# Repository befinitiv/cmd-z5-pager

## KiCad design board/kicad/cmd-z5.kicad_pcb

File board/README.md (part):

This document describes a PCB that acts as a replacement PCB for a Sony CMD-Z5 mobile phone. It is supposed to use the original screen and keyboard and turn the phone into a meshtastic device.

# Requirements

* nrf52840 CPU
* WIO-SX1262 wireless module with PCB antenna
* TBS M10N GPS with switched power line for power saving
* Battery charging and monitoring
* USB-C connector for charging and data/programming
* Use all keys of the original phone
* Use vibration motor, earpiece speaker and loudspeaker of original phone
* Use LEDs of original phone
* Uses small components so that PCB fits inside of housing
* Use 0402 passive components whenever possible
* Acceleromenter for movement detection
* Optimize for quiescent current. The device is also supposed to run in a low power mode where the idle current is expected to be below 20uA. This might require power switches to certain components.

# Component selection

LCSC part numbers were checked on 2026-10-02. Check stock again before ordering.

| Function | Part | LCSC | Package | Notes |
|---|---|---|---|---|
| MCU | Nordic nRF52840-QIAA-R | C190794 | aQFN-73 7×7 | Needs machine assembly |
| 32 MHz crystal | Yangxing X1E0000210163 | C91742 | 3225 | 10 pF, ±10 ppm |
| 32.768 kHz crystal | Epson X1A0000610006 | C99009 | 2012 | 7 pF |
| BLE antenna | Johanson 2450AT18A100E | C89334 | 1206 | Chip antenna with pi matching network |
| LoRa | Seeed Wio-SX1262 | – | 11.6×11 mm, 12 pins | **Not available on LCSC**; buy from Seeed. The standard version uses its IPEX connector and leaves the ANT pad (pin 9) unconnected; a PCB antenna needs the RF SMT-pin version (ask Seeed sales) |
| PMIC (charger, 2 bucks, 2 load switches, ADC, USB-C detection) | Nordic nPM1300-QEAA-R7 | C7501206 | QFN-32 5×5 | 0.8 µA battery current with a buck enabled, 370 nA in ship mode |
| GPS supply | TI TPS610997YFFR | C2072359 | DSBGA-6 | Fixed 5 V boost; EN fully disconnects the GPS (TBS M10N needs 3.6–5.5 V) |
| Accelerometer | ST LIS2DH12TR | C110926 | LGA-12 2×2 | About 2 µA in low-power motion detection; same WHO_AM_I as the LIS3DH. Alternative: LIS2DW12TR (C189624), lower current but needs its own driver |
| Earpiece amplifier | Diodes PAM8302AASCR | C113367 | MSOP-8 | BTL output for the floating earpiece; input from nRF PWM via RC filter |
| LED and loudspeaker drivers | Diodes DMG1024UV-7 | C2759893 | SOT-563 | Dual N-FET, low-side switches |
| Board LEDs (4×) | Everlight 19-217/GHC-YR1S2/3T | C72043 | 0603 | Green, 330 Ω each from VSYS, in parallel with the keyboard flex LEDs on the same low-side switch (Q1A, LED_EN) |
| Vibration motor driver | Diodes DMG1016UDW-7 | C211433 | SOT-363 | N+P pair, high-side switch (motor's other terminal is tied to GND) |
| Microphone preamp | TI TLV9001IDCKR | C398362 | SC-70-5 | 60 µA rail-to-rail op-amp, 33 dB gain for the original electret capsule, powered from an nPM1300 GPIO |
| Flyback diodes | 1N5819WS | C191023 | SOD-323 | For motor and loudspeaker |
| Power button diodes | BAT54C | C916424 | SOT-23 | Diode-OR of the power button to nPM1300 SHPHLD and an nRF GPIO |
| USB-C connector | GCT USB4105-GF-A | C3020560 | SMD | |
| USB ESD protection | ST USBLC6-2SC6 | C7519 | SOT-23-6 | |
| Display connector | Kinghelm KH-FPC0.5-H1.0SMT-26P-QCHF | C3250122 | SMD | 26-pin, 0.5 mm, 1.0 mm high, flip lock, double-sided contacts (display flex is top contact) |
| Keyboard flex connector | Kinghelm KH-FPC0.5-H1.0SMT-28P-QCHF | C3250123 | SMD | 28-pin, 0.5 mm, 1.0 mm high, double-sided contacts (keyboard flex is bottom contact) |
| Battery contacts (2×) | G-Switch GT-BTP30002-0500B-015A | C41378718 | SMD, horizontal | 2-pin, 3.0 mm pitch, side-push springs, 5.0 mm high, contact height 3.3 mm. One part per battery terminal |

The TCA8418 keypad controller was considered and dropped: it draws 3 µA in standby. The nRF52840 scans the matrix itself.

# Power architecture

```
USB-C ─► nPM1300 ─ VSYS ─┬─ BUCK2 3.0 V (150 kΩ on VSET2, on at boot) ─► nRF52840, LIS2DH12
                         │     ├─ LDSW1 ─► display VCC          (off in low-power mode)
                         │     ├─ LDSW2 ─► earpiece amplifier   (off in low-power mode)
                         │     └─ nPM1300 GPIO1 ─► microphone bias + preamp (off in low-power mode)
                         ├─ BUCK1 3.0 V (VSET1 grounded = off at boot) ─► Wio-SX1262 (enabled by firmware over I2C)
                         ├─ TPS610997 5 V (EN from nRF) ─► TBS M10N
                         └─ LED/loudspeaker common, vibration motor
```

* All logic runs from a single 3.0 V rail. The display needs 2.9 V, so 3.0 V needs no level shifters. The cost is roughly 0.5–1 dB less maximum TX power than at 3.3 V.
* BUCK2 is the always-on rail because a VSET resistor can set BUCK1 to at most 2.7 V at boot.
* Each nPM1300 buck supplies up to 200 mA. The SX1262 (about 118 mA in TX) has BUCK1 to itself.
* The nPM1300 starts with charging disabled. Firmware must configure the charge current, termination voltage and NTC over I2C. Battery voltage is read from the nPM1300 ADC, so there is no resistor divider.
* The nPM1300 CC1/CC2 pins connect directly to the USB-C connector. They have internal pull-downs, so no 5.1 kΩ resistors are needed.

# Low-power mode

Low-power mode means the LoRa radio is off; an SX1262 in RX draws about 5 mA. The device wakes on a key press, the lid, the power button, accelerometer motion or the RTC.

| Part | Current |
|---|---|
| nPM1300 (battery current, buck enabled) | 0.8 µA |
| nRF52840 asleep, RTC running, RAM retained | ~2–3 µA |
| LIS2DH12 motion detection | ~2 µA |
| SX1262, display, earpiece amplifier, microphone, GPS | ~0 (switched off) |
| Leakage (FETs, ESD diode, boost in shutdown) | < 1 µA |
| **Total** | **about 6–7 µA** |

Design rules to stay within this budget:

* **Lid switch:** it is probably closed while the phone is folded shut. With the nRF internal pull-up (about 13 kΩ) that is about 230 µA. Use a 4.7–10 MΩ external pull-up and disable the internal one. The same applies to the rotary encoder if it can rest with a contact closed.
* **Back-powering:** when the display, SX1262 or GPS is switched off, drive their signal lines low or set them as floating inputs.
* **Keypad wake:** in sleep, drive all matrix columns low and use GPIO SENSE on the rows, so any key wakes the nRF with no static current.
* **Power button:** connect it to nPM1300 SHPHLD (wakes from ship mode) and to an nRF GPIO through the BAT54C. SHPHLD has a 50 kΩ pull-up to VBAT, so a direct connection would put battery voltage on a 3.0 V GPIO.

# Design notes

* **Display bus:** the nRF52840 has no parallel bus peripheral, so the display is bit-banged. Put D0–D7 on 8 consecutive P0.x pins so one register write sets the byte. Tie `/CS` (pin 14) low, CS (pin 15) high and pin 9 low, leaving 11 signals: D0–D7, `/WR`, A0 and `/RESET`. P0.09/P0.10 need NFC disabled in the UICR if used.
* **Rotary encoder:** use the nRF quadrature decoder (QDEC).
* **GPS UART:** the M10N probably has 3.3 V I/O; put about 1 kΩ in series on its TX line into the nRF.
* **GPIO budget:** about 43 of the roughly 45 usable nRF52840 GPIOs are needed (48 minus the 32 kHz crystal and reset pins).
* **0402 passives:** use 0402 everywhere except the buck, boost and nRF DC/DC inductors (0603/0805 for current rating) and possibly a 22 µF bulk capacitor on VSYS (0603).
* **RTC battery (keyboard flex pin 23):** the nRF has no battery-backed domain. Leave it unconnected or route it to an ADC pin.
* **Battery:** assumed to be a 1S Li-ion/LiPo cell fitted in the original battery compartment. It connects through two G-Switch side-push spring contacts that replace the original contact block (2 mm pitch, contact height 3.5 mm, 6.8 mm high): J2 for + (pin 2 = VBAT) and J7 for − (pin 1 = GND). The other pin of each part and the fixing foot are not connected. The G-Switch contact sits 0.2 mm lower (3.3 mm) than the original contacts, and the two contacts of each part are 3.0 mm apart. Check that the used contact lands on the battery terminal. The footprint has a centre slot for the fixing foot because the drawing does not give the foot position for the 2-pin size; check against a sample. There is no thermistor contact, so NTC stays tied to GND. A 2.54 mm 1×2 pin header (J8, pin 1 = VBAT, pin 2 = GND) is in parallel for a wired battery or bench supply; it is not fitted (DNP).

# nRF52840 GPIO assignment

Package aQFN73. Pins marked "low frequency I/O only" in the nRF52840 product specification (signals up to 10 kHz) are used only for slow signals: keypad, buttons, encoder, interrupts and enables. Fast signals use the other pins: display bus, SPI, I2C, UART and audio PWM.

| Ball | GPIO | Side | Low freq only | Signal | Direction | Notes |
|---|---|---|---|---|---|---|
| D2 | P0.00 | top | | XL1 | – | 32.768 kHz crystal |
| F2 | P0.01 | top | | XL2 | – | 32.768 kHz crystal |
| G1 | P0.26 | top | | Display D7 | out | |
| H2 | P0.27 | top | | Loudspeaker PWM | out | Gate of DMG1024UV channel 2 |
| J1 | P0.04 | top | | *spare* (AIN2) | | Optional: RTC battery sense (keyboard flex pin 23) |
| K2 | P0.05 | top | | Microphone (AIN3) | analog in | TLV9001 preamp output, idles at VDD/2; SAADC single-ended |
| L1 | P0.06 | top | | Earpiece PWM | out | RC filter to PAM8302 input |
| M2 | P0.07 | top | | Vibration motor | out | Gate of DMG1016UDW N-FET |
| N1 | P0.08 | top | | LED control | out | Gate of DMG1024UV channel 1 |
| P2 | P1.08 | top | | I2C SDA | i/o | nPM1300, LIS2DH12 |
| R1 | P1.09 | top | | I2C SCL | out | nPM1300, LIS2DH12 |
| T2 | P0.11 | top | | GPS UART RX | in | From M10N TX, ~1 kΩ series |
| U1 | P0.12 | top | | GPS UART TX | out | To M10N RX |
| AD8 | P0.13 | right | | SX1262 SCK | out | |
| AC9 | P0.14 | right | | SX1262 MOSI | out | |
| AD10 | P0.15 | right | | SX1262 MISO | in | |
| AC11 | P0.16 | right | | SX1262 NSS | out | |
| AD12 | P0.17 | right | | Display A0 | out | Display pin 13 |
| AC13 | P0.18 | right | | nRESET | in | Pin reset, SWD connector |
| AC15 | P0.19 | right | | Display D0 | out | Display pin 24 |
| AD16 | P0.20 | right | | Display D1 | out | Display pin 23 |
| AC17 | P0.21 | right | | Display D2 | out | Display pin 22 |
| AD18 | P0.22 | right | | Display D3 | out | Display pin 21 |
| AC19 | P0.23 | right | | Display D4 | out | Display pin 20 |
| AD20 | P0.24 | right | | Display D5 | out | Display pin 19 |
| AC21 | P0.25 | right | | Display D6 | out | Display pin 18 (D7 = P0.26, display pin 17) |
| AD22 | P1.00 | right | | Display /WR | out | Display pin 10 |
| L24 | P0.09 | bottom | yes | SX1262 RF switch | out | NFC pin; Wio-SX1262 pin 1 `RF_SW`, driven as `SX126X_RXEN` in Meshtastic |
| J24 | P0.10 | bottom | yes | SX1262 NRESET | out | NFC pin |
| Y23 | P1.01 | bottom | yes | SX1262 BUSY | in | |
| W24 | P1.02 | bottom | yes | SX1262 DIO1 | in | IRQ |
| V23 | P1.03 | bottom | yes | GPS power enable | out | TPS610997 EN |
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
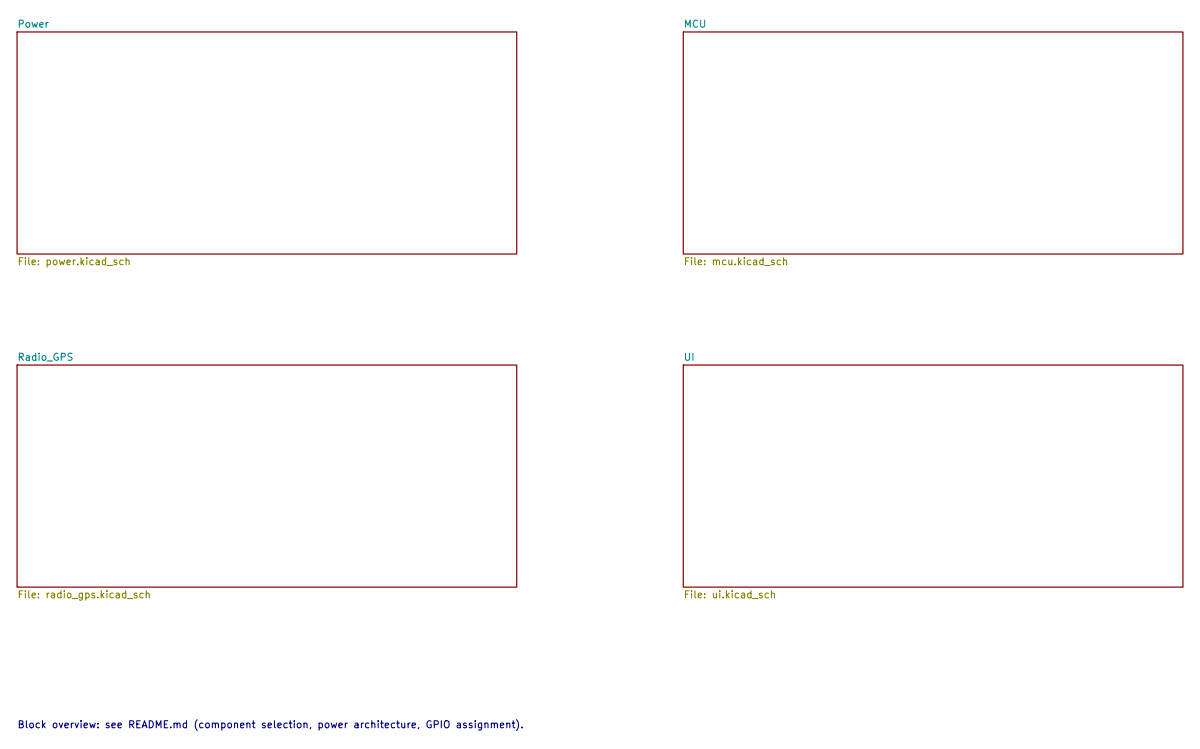
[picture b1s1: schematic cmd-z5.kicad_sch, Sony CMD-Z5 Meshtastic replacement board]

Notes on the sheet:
Block overview: see README.md (component selection, power architecture, GPIO assignment).

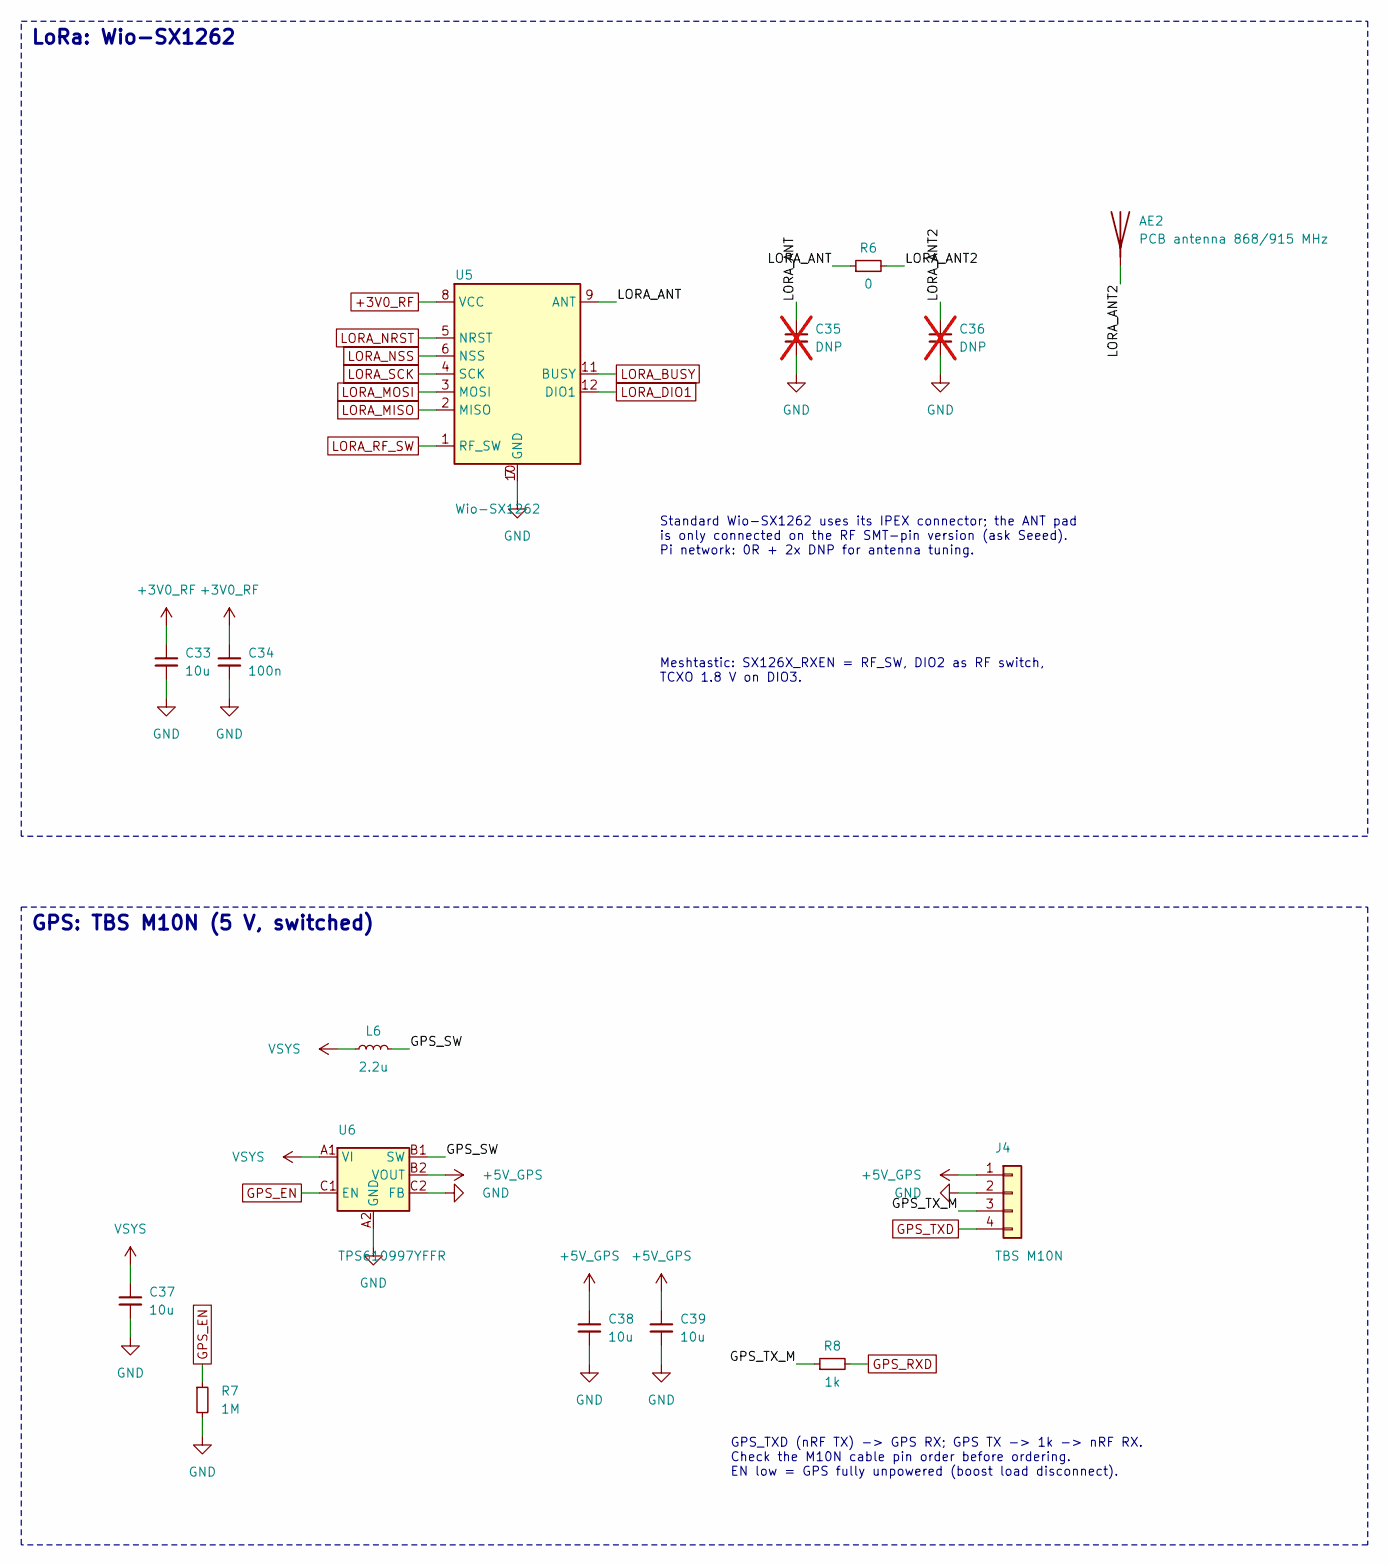
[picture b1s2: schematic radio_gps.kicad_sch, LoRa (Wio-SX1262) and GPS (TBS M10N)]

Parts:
AE2: PCB antenna 868/915 MHz; Texas_SWRA416_868MHz_915MHz_Mirrored
C33, C37, C38, C39: 10u; C_0603_1608Metric
C34: 100n; C_0402_1005Metric
C35, C36: DNP; C_0402_1005Metric; not fitted
J4: TBS M10N; SolderPads_1x04_P2.00mm_SMD
L6: 2.2u; L_0805_2012Metric
R6: 0; R_0402_1005Metric
R7: 1M; R_0402_1005Metric
R8: 1k; R_0402_1005Metric
U5: Wio-SX1262; Seeed_Wio-SX1262
U6: TPS610997YFFR; Texas_DSBGA-6_0.855x1.255mm_Layout2x3_P0.4mm_LevelB; LCSC C2072359

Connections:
+3V0_RF: C33.1, C34.1, U5.8 (VCC); also elsewhere on the board
+5V_GPS: C38.1, C39.1, J4.1, U6.B2 (VOUT)
/Radio_GPS/GPS_SW: L6.2, U6.B1 (SW)
/Radio_GPS/GPS_TX_M: J4.3, R8.1
/Radio_GPS/LORA_ANT: C35.1, R6.1, U5.9 (ANT)
/Radio_GPS/LORA_ANT2: AE2.1, C36.1, R6.2
GND: C33.2, C34.2, C35.2, C36.2, C37.2, C38.2, C39.2, J4.2, R7.2, U5.7 (GND), U5.10 (GND), U6.A2 (GND), U6.C2 (FB); also elsewhere on the board
GPS_EN: R7.1, U6.C1 (EN); also elsewhere on the board
GPS_RXD: R8.2; also elsewhere on the board
GPS_TXD: J4.4; also elsewhere on the board
LORA_BUSY: U5.11 (BUSY); also elsewhere on the board
LORA_DIO1: U5.12 (DIO1); also elsewhere on the board
LORA_MISO: U5.2 (MISO); also elsewhere on the board
LORA_MOSI: U5.3 (MOSI); also elsewhere on the board
LORA_NRST: U5.5 (NRST); also elsewhere on the board
LORA_NSS: U5.6 (NSS); also elsewhere on the board
LORA_RF_SW: U5.1 (RF_SW); also elsewhere on the board
LORA_SCK: U5.4 (SCK); also elsewhere on the board
VSYS: C37.1, L6.1, U6.A1 (VI); also elsewhere on the board

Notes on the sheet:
Standard Wio-SX1262 uses its IPEX connector; the ANT pad is only connected on the RF SMT-pin version (ask Seeed). Pi network: 0R + 2x DNP for antenna tuning.
GPS_TXD (nRF TX) -> GPS RX; GPS TX -> 1k -> nRF RX. Check the M10N cable pin order before ordering. EN low = GPS fully unpowered (boost load disconnect).
Meshtastic: SX126X_RXEN = RF_SW, DIO2 as RF switch, TCXO 1.8 V on DIO3.
LoRa: Wio-SX1262
GPS: TBS M10N (5 V, switched)

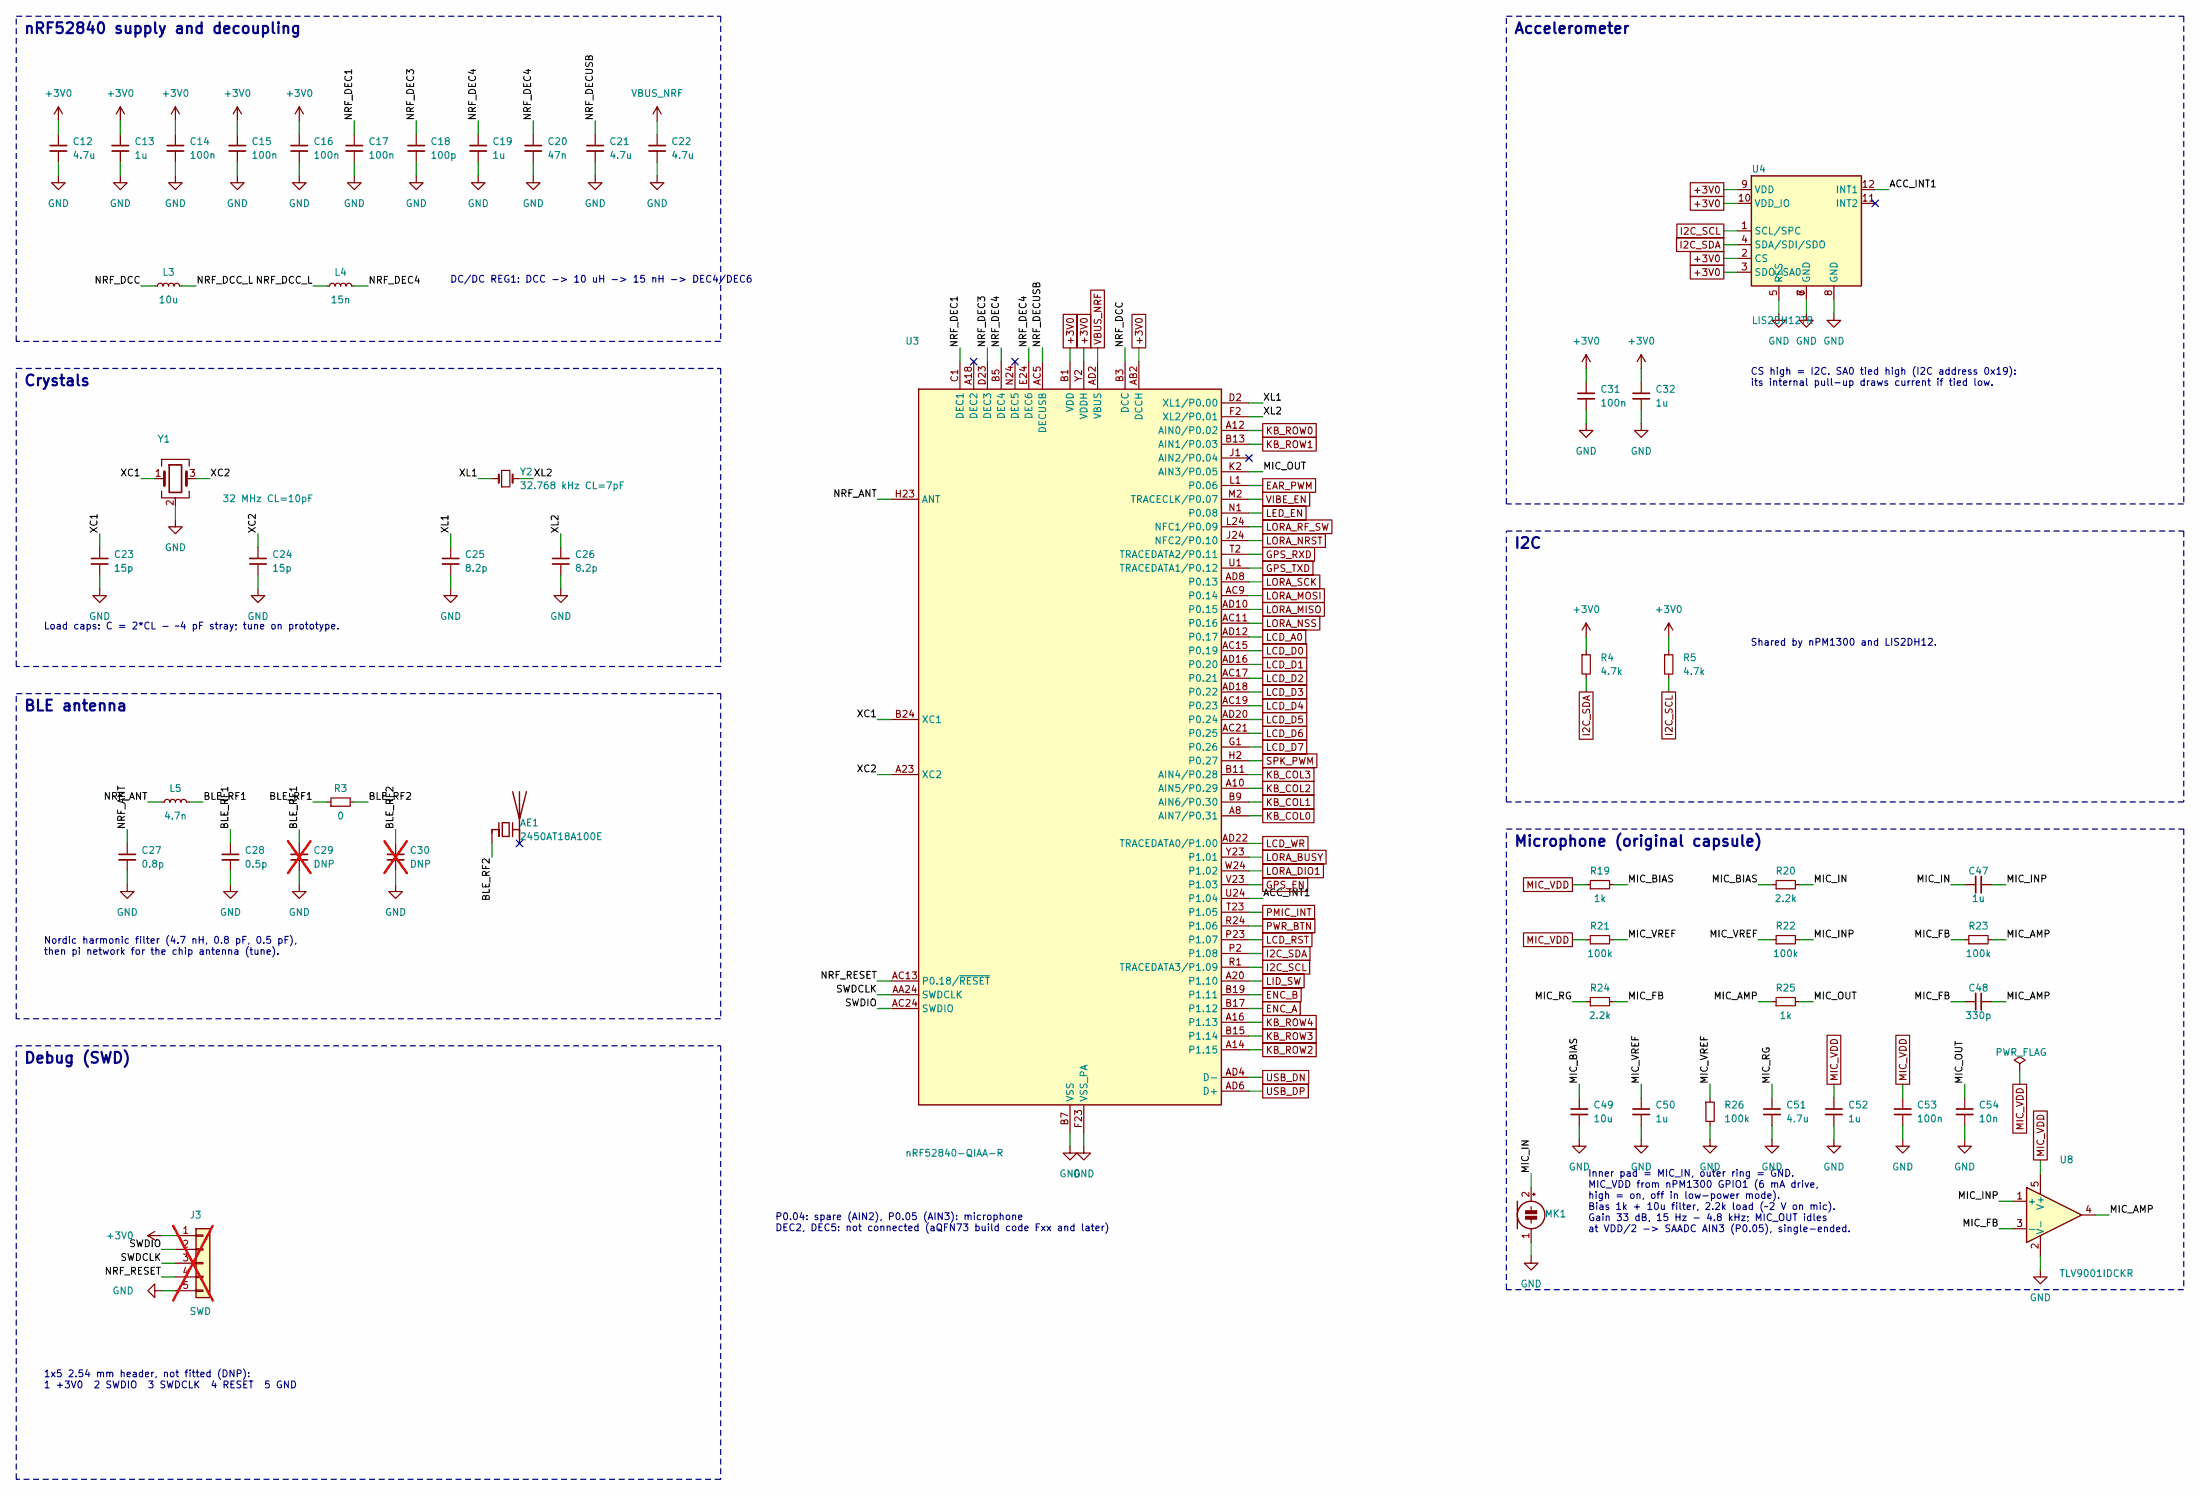
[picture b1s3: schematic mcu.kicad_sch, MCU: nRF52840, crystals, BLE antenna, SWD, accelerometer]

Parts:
AE1: 2450AT18A100E; Johanson_2450AT18x100; LCSC C89334
C12, C21, C51: 4.7u; C_0402_1005Metric
C13, C19, C32, C47, C50, C52: 1u; C_0402_1005Metric
C14, C15, C16, C17, C31, C53: 100n; C_0402_1005Metric
C18: 100p; C_0402_1005Metric
C20: 47n; C_0402_1005Metric
C22: 4.7u; C_0603_1608Metric
C23, C24: 15p; C_0402_1005Metric
C25, C26: 8.2p; C_0402_1005Metric
C27: 0.8p; C_0402_1005Metric
C28: 0.5p; C_0402_1005Metric
C29, C30: DNP; C_0402_1005Metric; not fitted
C48: 330p; C_0402_1005Metric
C49: 10u; C_0603_1608Metric
C54: 10n; C_0402_1005Metric
J3: SWD; PinHeader_1x05_P2.54mm_Vertical; not fitted
L3: 10u; L_0603_1608Metric
L4: 15n; L_0402_1005Metric
L5: 4.7n; L_0402_1005Metric
MK1: Capsule mic (original); MIC_Contact_Concentric_D6.2mm
R3: 0; R_0402_1005Metric
R4, R5: 4.7k; R_0402_1005Metric
R19, R25: 1k; R_0402_1005Metric
R20, R24: 2.2k; R_0402_1005Metric
R21, R22, R23, R26: 100k; R_0402_1005Metric
U3: nRF52840-QIAA-R; Nordic_AQFN-73-1EP_7x7mm_P0.5mm; LCSC C190794
U4: LIS2DH12TR; LGA-12_2x2mm_P0.5mm; LCSC C110926
U8: TLV9001IDCKR; SOT-353_SC-70-5; LCSC C398362
Y1: 32 MHz CL=10pF; Crystal_SMD_3225-4Pin_3.2x2.5mm; MPN X1E0000210163; LCSC C91742
Y2: 32.768 kHz CL=7pF; Crystal_SMD_2012-2Pin_2.0x1.2mm; MPN X1A0000610006; LCSC C99009

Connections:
+3V0: C12.1, C13.1, C14.1, C15.1, C16.1, C31.1, C32.1, J3.1, R4.1, R5.1, U3.A22 (VDD), U3.AB2 (DCCH), U3.AD14 (VDD), U3.AD23 (VDD), U3.B1 (VDD), U3.W1 (VDD), U3.Y2 (VDDH), U4.2 (CS), U4.3 (SDO/SA0), U4.9 (VDD), U4.10 (VDD_IO); also elsewhere on the board
/MCU/ACC_INT1: U3.U24 (P1.04), U4.12 (INT1)
/MCU/BLE_RF1: C28.1, C29.1, L5.2, R3.1
/MCU/BLE_RF2: AE1.1 (FEED_1), C30.1, R3.2
/MCU/MIC_AMP: C48.2, R23.2, R25.1, U8.4
/MCU/MIC_BIAS: C49.1, R19.2, R20.1
/MCU/MIC_FB: C48.1, R23.1, R24.2, U8.3 (-)
/MCU/MIC_IN: C47.1, MK1.2 (+), R20.2
/MCU/MIC_INP: C47.2, R22.2, U8.1 (+)
/MCU/MIC_OUT: C54.1, R25.2, U3.K2 (AIN3/P0.05)
/MCU/MIC_RG: C51.1, R24.1
/MCU/MIC_VREF: C50.1, R21.2, R22.1, R26.1
/MCU/NRF_ANT: C27.1, L5.1, U3.H23 (ANT)
/MCU/NRF_DCC: L3.1, U3.B3 (DCC)
/MCU/NRF_DCC_L: L3.2, L4.1
/MCU/NRF_DEC1: C17.1, U3.C1 (DEC1)
/MCU/NRF_DEC3: C18.1, U3.D23 (DEC3)
/MCU/NRF_DEC4: C19.1, C20.1, L4.2, U3.B5 (DEC4), U3.E24 (DEC6)
/MCU/NRF_DECUSB: C21.1, U3.AC5 (DECUSB)
/MCU/NRF_RESET: J3.4, U3.AC13 (P0.18/~RESET)
/MCU/SWDCLK: J3.3, U3.AA24 (SWDCLK)
/MCU/SWDIO: J3.2, U3.AC24 (SWDIO)
/MCU/XC1: C23.1, U3.B24 (XC1), Y1.1
/MCU/XC2: C24.1, U3.A23 (XC2), Y1.3
/MCU/XL1: C25.1, U3.D2 (XL1/P0.00), Y2.1
/MCU/XL2: C26.1, U3.F2 (XL2/P0.01), Y2.2
EAR_PWM: U3.L1 (P0.06); also elsewhere on the board
ENC_A: U3.B17 (P1.12); also elsewhere on the board
ENC_B: U3.B19 (P1.11); also elsewhere on the board
GND: C12.2, C13.2, C14.2, C15.2, C16.2, C17.2, C18.2, C19.2, C20.2, C21.2, C22.2, C23.2, C24.2, C25.2, C26.2, C27.2, C28.2, C29.2, C30.2, C31.2, C32.2, C49.2, C50.2, C51.2, C52.2, C53.2, C54.2, J3.5, MK1.1 (-), R26.2, U3.B7 (VSS), U3.EP (VSS), U3.F23 (VSS_PA), U4.5 (RES), U4.6 (GND), U4.7 (GND), U4.8 (GND), U8.2 (V-), Y1.2 (G), Y1.4 (G); also elsewhere on the board
GPS_EN: U3.V23 (P1.03); also elsewhere on the board
GPS_RXD: U3.T2 (TRACEDATA2/P0.11); also elsewhere on the board
GPS_TXD: U3.U1 (TRACEDATA1/P0.12); also elsewhere on the board
I2C_SCL: R5.2, U3.R1 (TRACEDATA3/P1.09), U4.1 (SCL/SPC); also elsewhere on the board
I2C_SDA: R4.2, U3.P2 (P1.08), U4.4 (SDA/SDI/SDO); also elsewhere on the board
KB_COL0: U3.A8 (AIN7/P0.31); also elsewhere on the board
KB_COL1: U3.B9 (AIN6/P0.30); also elsewhere on the board
KB_COL2: U3.A10 (AIN5/P0.29); also elsewhere on the board
KB_COL3: U3.B11 (AIN4/P0.28); also elsewhere on the board
KB_ROW0: U3.A12 (AIN0/P0.02); also elsewhere on the board
KB_ROW1: U3.B13 (AIN1/P0.03); also elsewhere on the board
KB_ROW2: U3.A14 (P1.15); also elsewhere on the board
KB_ROW3: U3.B15 (P1.14); also elsewhere on the board
KB_ROW4: U3.A16 (P1.13); also elsewhere on the board
LCD_A0: U3.AD12 (P0.17); also elsewhere on the board
LCD_D0: U3.AC15 (P0.19); also elsewhere on the board
LCD_D1: U3.AD16 (P0.20); also elsewhere on the board
LCD_D2: U3.AC17 (P0.21); also elsewhere on the board
LCD_D3: U3.AD18 (P0.22); also elsewhere on the board
LCD_D4: U3.AC19 (P0.23); also elsewhere on the board
LCD_D5: U3.AD20 (P0.24); also elsewhere on the board
LCD_D6: U3.AC21 (P0.25); also elsewhere on the board
LCD_D7: U3.G1 (P0.26); also elsewhere on the board
LCD_RST: U3.P23 (P1.07); also elsewhere on the board
LCD_WR: U3.AD22 (TRACEDATA0/P1.00); also elsewhere on the board
LED_EN: U3.N1 (P0.08); also elsewhere on the board
LID_SW: U3.A20 (P1.10); also elsewhere on the board
LORA_BUSY: U3.Y23 (P1.01); also elsewhere on the board
LORA_DIO1: U3.W24 (P1.02); also elsewhere on the board
LORA_MISO: U3.AD10 (P0.15); also elsewhere on the board
LORA_MOSI: U3.AC9 (P0.14); also elsewhere on the board
LORA_NRST: U3.J24 (NFC2/P0.10); also elsewhere on the board
LORA_NSS: U3.AC11 (P0.16); also elsewhere on the board
LORA_RF_SW: U3.L24 (NFC1/P0.09); also elsewhere on the board
LORA_SCK: U3.AD8 (P0.13); also elsewhere on the board
MIC_VDD: C52.1, C53.1, R19.1, R21.1, U8.5 (V+); also elsewhere on the board
PMIC_INT: U3.T23 (P1.05); also elsewhere on the board
PWR_BTN: U3.R24 (P1.06); also elsewhere on the board
SPK_PWM: U3.H2 (P0.27); also elsewhere on the board
USB_DN: U3.AD4 (D-); also elsewhere on the board
USB_DP: U3.AD6 (D+); also elsewhere on the board
VBUS_NRF: C22.1, U3.AD2 (VBUS); also elsewhere on the board
VIBE_EN: U3.M2 (TRACECLK/P0.07); also elsewhere on the board

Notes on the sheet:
Nordic harmonic filter (4.7 nH, 0.8 pF, 0.5 pF), then pi network for the chip antenna (tune).
Accelerometer
Debug (SWD)
I2C
nRF52840 supply and decoupling
Microphone (original capsule)
Inner pad = MIC_IN, outer ring = GND. MIC_VDD from nPM1300 GPIO1 (6 mA drive, high = on, off in low-power mode). Bias 1k + 10u filter, 2.2k load (~2 V on mic). Gain 33 dB, 15 Hz - 4.8 kHz; MIC_OUT idles at VDD/2 -> SAADC AIN3 (P0.05), single-ended.
1x5 2.54 mm header, not fitted (DNP): 1 +3V0 2 SWDIO 3 SWDCLK 4 RESET 5 GND
CS high = I2C. SA0 tied high (I2C address 0x19): its internal pull-up draws current if tied low.
BLE antenna
Load caps: C = 2*CL - ~4 pF stray; tune on prototype.
DC/DC REG1: DCC -> 10 uH -> 15 nH -> DEC4/DEC6
Shared by nPM1300 and LIS2DH12.
Crystals
P0.04: spare (AIN2), P0.05 (AIN3): microphone DEC2, DEC5: not connected (aQFN73 build code Fxx and later)

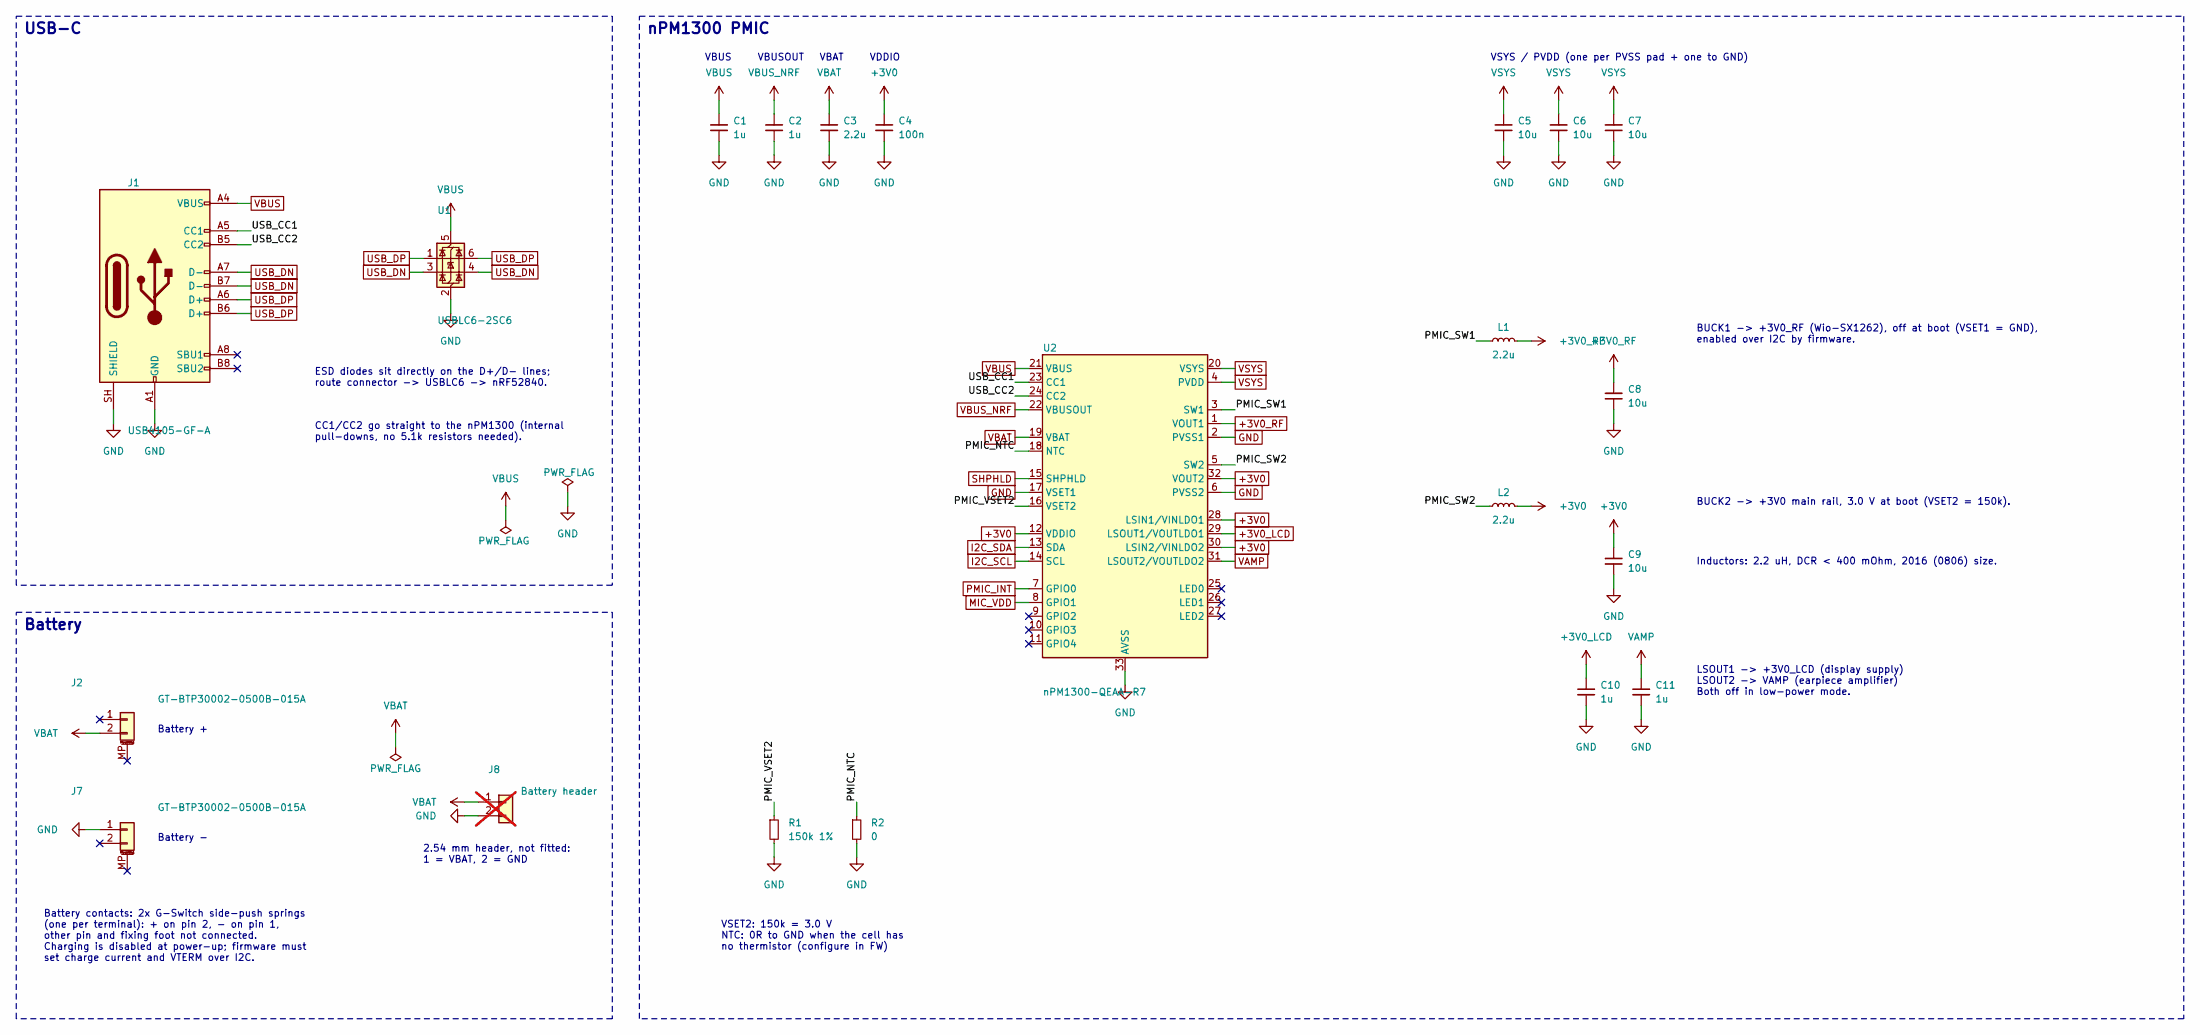
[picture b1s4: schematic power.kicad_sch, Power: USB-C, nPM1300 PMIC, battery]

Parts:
C1: 1u; C_0603_1608Metric
C2, C10, C11: 1u; C_0402_1005Metric
C3: 2.2u; C_0603_1608Metric
C4: 100n; C_0402_1005Metric
C5, C6, C7, C8, C9: 10u; C_0603_1608Metric
J1: USB4105-GF-A; USB_C_Receptacle_GCT_USB4105-xx-A_16P_TopMnt_Horizontal; LCSC C3020560
J2, J7: GT-BTP30002-0500B-015A; BAT-SMD_2P-P3.00_G-Switch_GT-BTP30002-0500B-015A; LCSC C41378718
J8: Battery header; PinHeader_1x02_P2.54mm_Vertical; not fitted
L1, L2: 2.2u; L_0805_2012Metric
R1: 150k 1%; R_0402_1005Metric
R2: 0; R_0402_1005Metric
U1: USBLC6-2SC6; SOT-23-6; LCSC C7519
U2: nPM1300-QEAA-R7; QFN-32-1EP_5x5mm_P0.5mm_EP3.45x3.45mm; LCSC C7501206

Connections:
+3V0: C4.1, C9.1, L2.2, U2.12 (VDDIO), U2.28 (LSIN1/VINLDO1), U2.30 (LSIN2/VINLDO2), U2.32 (VOUT2); also elsewhere on the board
+3V0_LCD: C10.1, U2.29 (LSOUT1/VOUTLDO1); also elsewhere on the board
+3V0_RF: C8.1, L1.2, U2.1 (VOUT1); also elsewhere on the board
/Power/PMIC_NTC: R2.1, U2.18 (NTC)
/Power/PMIC_SW1: L1.1, U2.3 (SW1)
/Power/PMIC_SW2: L2.1, U2.5 (SW2)
/Power/PMIC_VSET2: R1.1, U2.16 (VSET2)
/Power/USB_CC1: J1.A5 (CC1), U2.23 (CC1)
/Power/USB_CC2: J1.B5 (CC2), U2.24 (CC2)
GND: C1.2, C2.2, C3.2, C4.2, C5.2, C6.2, C7.2, C8.2, C9.2, C10.2, C11.2, J1.A1 (GND), J1.A12 (GND), J1.B1 (GND), J1.B12 (GND), J1.SH (SHIELD), J7.1 (Pin_1_1), J8.2, R1.2, R2.2, U1.2 (GND), U2.2 (PVSS1), U2.6 (PVSS2), U2.17 (VSET1), U2.33 (AVSS); also elsewhere on the board
I2C_SCL: U2.14 (SCL); also elsewhere on the board
I2C_SDA: U2.13 (SDA); also elsewhere on the board
MIC_VDD: U2.8 (GPIO1); also elsewhere on the board
PMIC_INT: U2.7 (GPIO0); also elsewhere on the board
SHPHLD: U2.15 (SHPHLD); also elsewhere on the board
USB_DN: J1.A7 (D-), J1.B7 (D-), U1.3 (I/O2), U1.4 (I/O2); also elsewhere on the board
USB_DP: J1.A6 (D+), J1.B6 (D+), U1.1 (I/O1), U1.6 (I/O1); also elsewhere on the board
VAMP: C11.1, U2.31 (LSOUT2/VOUTLDO2); also elsewhere on the board
VBAT: C3.1, J2.2 (Pin_2_2), J8.1, U2.19 (VBAT)
VBUS: C1.1, J1.A4 (VBUS), J1.A9 (VBUS), J1.B4 (VBUS), J1.B9 (VBUS), U1.5 (VBUS), U2.21 (VBUS)
VBUS_NRF: C2.1, U2.22 (VBUSOUT); also elsewhere on the board
VSYS: C5.1, C6.1, C7.1, U2.4 (PVDD), U2.20 (VSYS); also elsewhere on the board

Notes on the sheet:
VSET2: 150k = 3.0 V NTC: 0R to GND when the cell has no thermistor (configure in FW)
nPM1300 PMIC
Inductors: 2.2 uH, DCR < 400 mOhm, 2016 (0806) size.
BUCK1 -> +3V0_RF (Wio-SX1262), off at boot (VSET1 = GND), enabled over I2C by firmware.
CC1/CC2 go straight to the nPM1300 (internal pull-downs, no 5.1k resistors needed).
Battery -
ESD diodes sit directly on the D+/D- lines; route connector -> USBLC6 -> nRF52840.
VBUS VBUSOUT VBAT VDDIO
VSYS / PVDD (one per PVSS pad + one to GND)
2.54 mm header, not fitted: 1 = VBAT, 2 = GND
Battery +
BUCK2 -> +3V0 main rail, 3.0 V at boot (VSET2 = 150k).
Battery contacts: 2x G-Switch side-push springs (one per terminal): + on pin 2, - on pin 1, other pin and fixing foot not connected. Charging is disabled at power-up; firmware must set charge current and VTERM over I2C.
LSOUT1 -> +3V0_LCD (display supply) LSOUT2 -> VAMP (earpiece amplifier) Both off in low-power mode.
Battery
USB-C

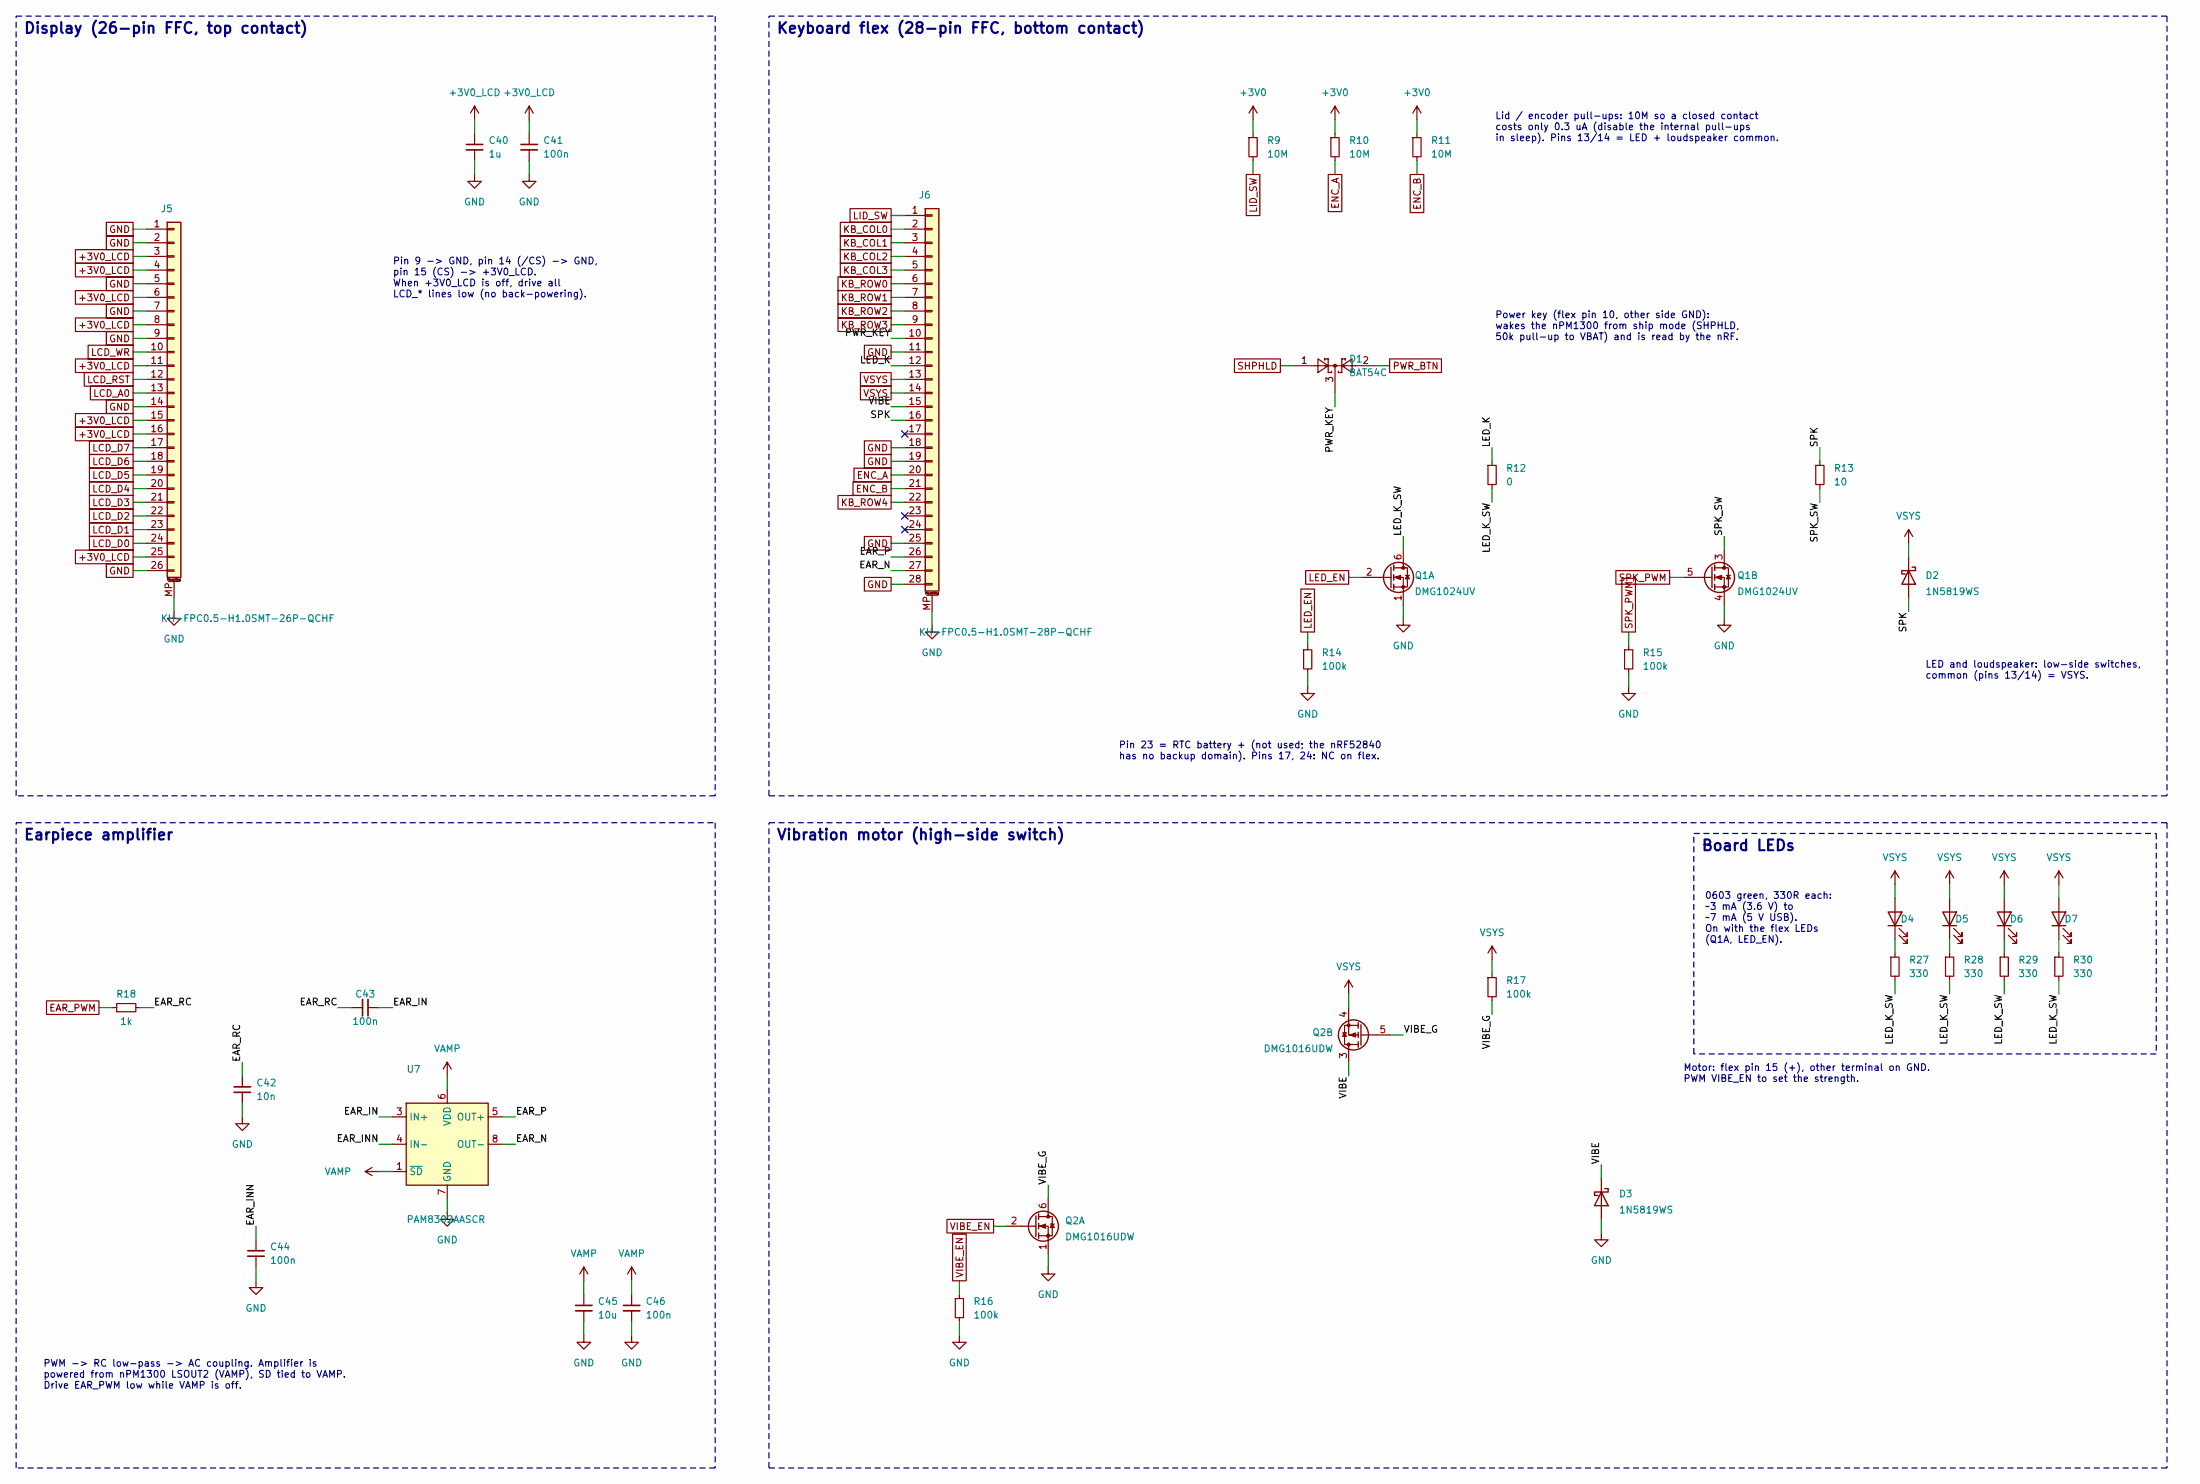
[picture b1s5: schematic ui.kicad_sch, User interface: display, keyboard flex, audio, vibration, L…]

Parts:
C40: 1u; C_0402_1005Metric
C41, C43, C44, C46: 100n; C_0402_1005Metric
C42: 10n; C_0402_1005Metric
C45: 10u; C_0603_1608Metric
D1: BAT54C; SOT-23; LCSC C916424
D2, D3: 1N5819WS; D_SOD-323; LCSC C191023
D4, D5, D6, D7: green; LED_0603_1608Metric; MPN 19-217/GHC-YR1S2/3T; LCSC C72043
J5: KH-FPC0.5-H1.0SMT-26P-QCHF; FPC-SMD_26P-P0.50_KH-FPC0.5-H1.0SMT-26P-QCHF; LCSC C3250122
J6: KH-FPC0.5-H1.0SMT-28P-QCHF; FPC-SMD_28P-P0.50_KH-FPC0.5-H1.0SMT-28P-QCHF; LCSC C3250123
Q1: DMG1024UV; SOT-563; LCSC C2759893
Q2: DMG1016UDW; SOT-363_SC-70-6; LCSC C211433
R9, R10, R11: 10M; R_0402_1005Metric
R12: 0; R_0402_1005Metric
R13: 10; R_0603_1608Metric
R14, R15, R16, R17: 100k; R_0402_1005Metric
R18: 1k; R_0402_1005Metric
R27, R28, R29, R30: 330; R_0402_1005Metric
U7: PAM8302AASCR; MSOP-8_3x3mm_P0.65mm; LCSC C113367

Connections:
+3V0: R9.1, R10.1, R11.1; also elsewhere on the board
+3V0_LCD: C40.1, C41.1, J5.3, J5.4, J5.6, J5.8, J5.11, J5.15, J5.16, J5.25; also elsewhere on the board
/UI/EAR_IN: C43.2, U7.3 (IN+)
/UI/EAR_INN: C44.1, U7.4 (IN-)
/UI/EAR_N: J6.27, U7.8 (OUT-)
/UI/EAR_P: J6.26, U7.5 (OUT+)
/UI/EAR_RC: C42.1, C43.1, R18.2
/UI/LED_K: J6.12, R12.1
/UI/LED_K_SW: Q1.6 (D), R12.2, R27.2, R28.2, R29.2, R30.2
/UI/PWR_KEY: D1.3, J6.10
/UI/SPK: D2.2 (A), J6.16, R13.1
/UI/SPK_SW: Q1.3 (D), R13.2
/UI/VIBE: D3.1 (K), J6.15, Q2.3 (D)
/UI/VIBE_G: Q2.5 (G), Q2.6 (D), R17.2
EAR_PWM: R18.1; also elsewhere on the board
ENC_A: J6.20, R10.2; also elsewhere on the board
ENC_B: J6.21, R11.2; also elsewhere on the board
GND: C40.2, C41.2, C42.2, C44.2, C45.2, C46.2, D3.2 (A), J5.1, J5.2, J5.5, J5.7, J5.9, J5.14, J5.26, J5.MP (MountPin), J6.11, J6.18, J6.19, J6.25, J6.28, J6.MP (MountPin), Q1.1 (S), Q1.4 (S), Q2.1 (S), R14.2, R15.2, R16.2, U7.7 (GND); also elsewhere on the board
KB_COL0: J6.2; also elsewhere on the board
KB_COL1: J6.3; also elsewhere on the board
KB_COL2: J6.4; also elsewhere on the board
KB_COL3: J6.5; also elsewhere on the board
KB_ROW0: J6.6; also elsewhere on the board
KB_ROW1: J6.7; also elsewhere on the board
KB_ROW2: J6.8; also elsewhere on the board
KB_ROW3: J6.9; also elsewhere on the board
KB_ROW4: J6.22; also elsewhere on the board
LCD_A0: J5.13; also elsewhere on the board
LCD_D0: J5.24; also elsewhere on the board
LCD_D1: J5.23; also elsewhere on the board
LCD_D2: J5.22; also elsewhere on the board
LCD_D3: J5.21; also elsewhere on the board
LCD_D4: J5.20; also elsewhere on the board
LCD_D5: J5.19; also elsewhere on the board
LCD_D6: J5.18; also elsewhere on the board
LCD_D7: J5.17; also elsewhere on the board
LCD_RST: J5.12; also elsewhere on the board
LCD_WR: J5.10; also elsewhere on the board
LED_EN: Q1.2 (G), R14.1; also elsewhere on the board
LID_SW: J6.1, R9.2; also elsewhere on the board
unnamed: D4.1 (K), R27.1
unnamed: D5.1 (K), R28.1
unnamed: D6.1 (K), R29.1
unnamed: D7.1 (K), R30.1
PWR_BTN: D1.2; also elsewhere on the board
SHPHLD: D1.1; also elsewhere on the board
SPK_PWM: Q1.5 (G), R15.1; also elsewhere on the board
VAMP: C45.1, C46.1, U7.1 (~SD), U7.6 (VDD); also elsewhere on the board
VIBE_EN: Q2.2 (G), R16.1; also elsewhere on the board
VSYS: D2.1 (K), D4.2 (A), D5.2 (A), D6.2 (A), D7.2 (A), J6.13, J6.14, Q2.4 (S), R17.1; also elsewhere on the board

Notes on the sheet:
0603 green, 330R each: ~3 mA (3.6 V) to ~7 mA (5 V USB). On with the flex LEDs (Q1A, LED_EN).
Earpiece amplifier
Motor: flex pin 15 (+), other terminal on GND. PWM VIBE_EN to set the strength.
Lid / encoder pull-ups: 10M so a closed contact costs only 0.3 uA (disable the internal pull-ups in sleep). Pins 13/14 = LED + loudspeaker common.
Power key (flex pin 10, other side GND): wakes the nPM1300 from ship mode (SHPHLD, 50k pull-up to VBAT) and is read by the nRF.
Pin 9 -> GND, pin 14 (/CS) -> GND, pin 15 (CS) -> +3V0_LCD. When +3V0_LCD is off, drive all LCD_* lines low (no back-powering).
PWM -> RC low-pass -> AC coupling. Amplifier is powered from nPM1300 LSOUT2 (VAMP), SD tied to VAMP. Drive EAR_PWM low while VAMP is off.
Board LEDs
Vibration motor (high-side switch)
Keyboard flex (28-pin FFC, bottom contact)
LED and loudspeaker: low-side switches, common (pins 13/14) = VSYS.
Pin 23 = RTC battery + (not used; the nRF52840 has no backup domain). Pins 17, 24: NC on flex.
Display (26-pin FFC, top contact)
